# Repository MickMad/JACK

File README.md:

#JACK
##Just Another Cortex Kit

A Cortex-M0+ development kit with an Atmel SAM D21, a USB device port, a regulator, some passives, a programming header, and breakout headers.

Arduino Zero compatible.

Software is here:

https://github.com/MickMad/ArduinoCore-samd/

```
Copyright © Michele Perla 2015

This documentation describes Open Hardware and is licensed under the CERN OHL v. 1.2.
You may redistribute and modify this documentation under the terms of the CERN OHL v.1.2. 
(http://ohwr.org/cernohl). This documentation is distributed
WITHOUT ANY EXPRESS OR IMPLIED WARRANTY, INCLUDING OF
MERCHANTABILITY, SATISFACTORY QUALITY AND FITNESS FOR A
PARTICULAR PURPOSE. Please see the CERN OHL v.1.2 for applicable
conditions
```

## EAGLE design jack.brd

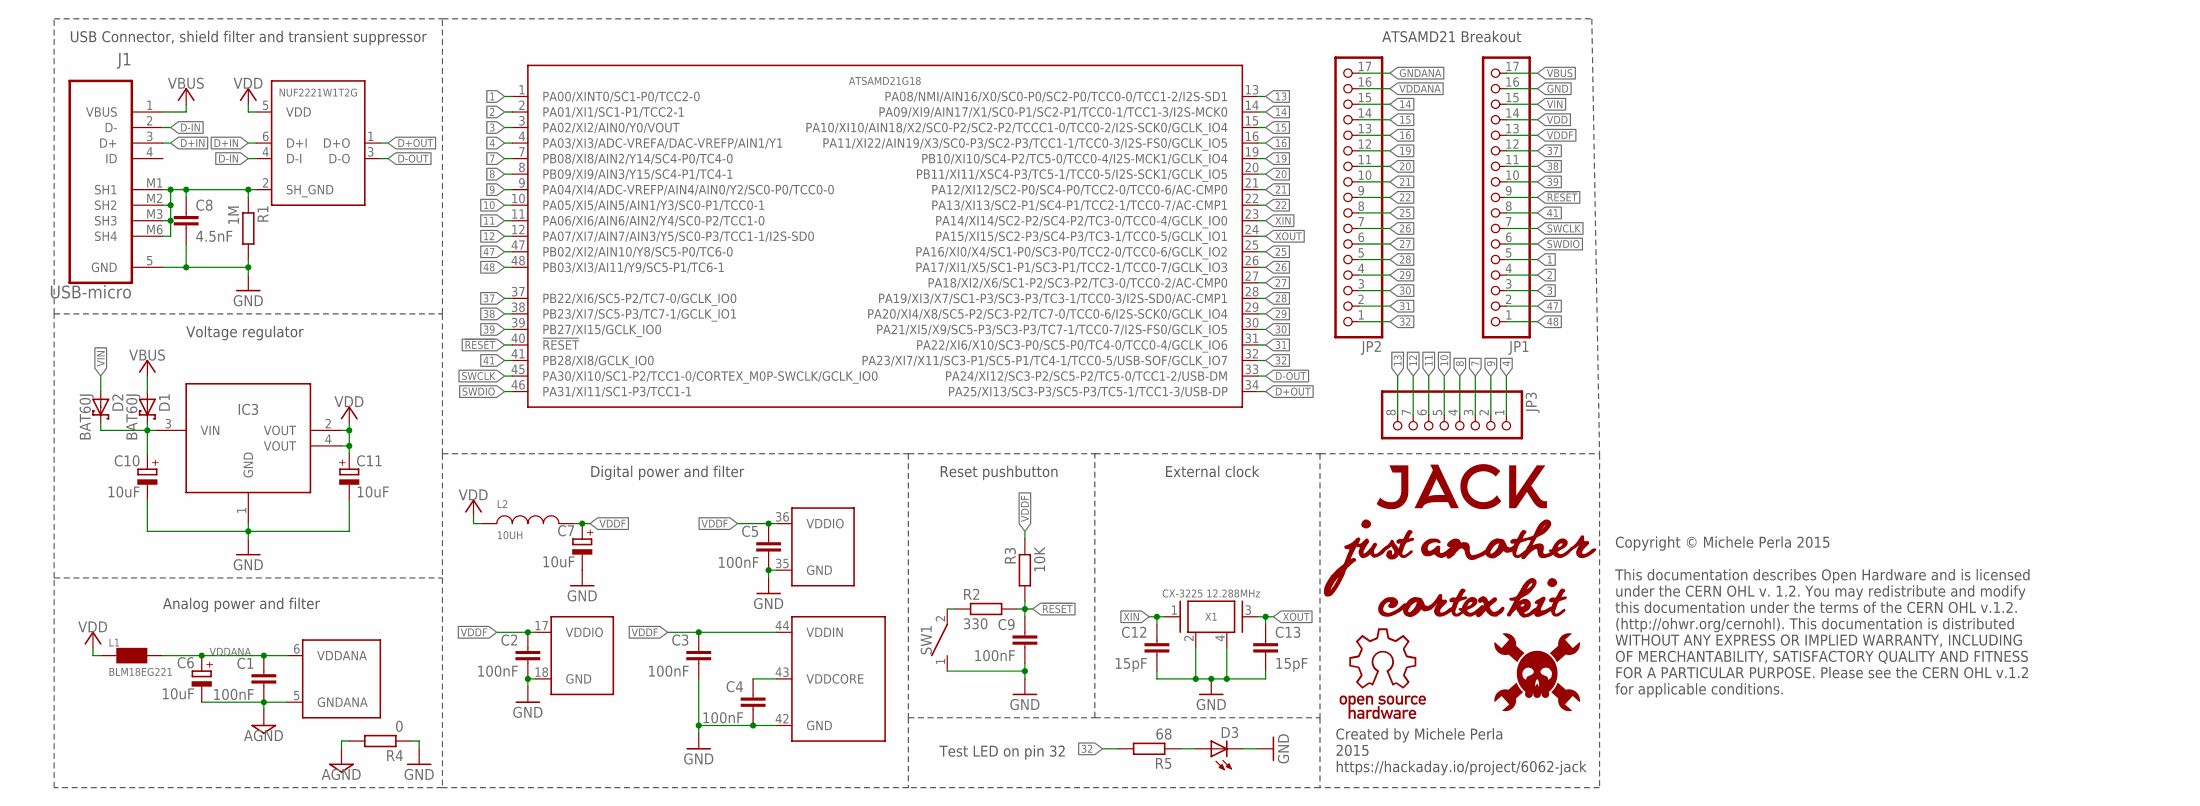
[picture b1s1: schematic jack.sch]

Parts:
C1, C2, C3, C4, C5, C9: 100nF; C0402
C6, C7, C10, C11: 10uF; CT3216
C8: 4.5nF; C0402
C12, C13: 15pF; C0402
D1, D2: BAT60J; SOD323_ST
D3: LED; LED-0603
IC1: NUF2221W1T2G; SOT-363
IC2: ATSAMD21G18; TQFP48
IC3: LDO; SOT-223-3
J1: USB-micro; MOLEX_47346-0001
JP1, JP2: PINHD-1X17; 1X17
JP3: PINHD-1X8; 1X08
L1: BLM18EG221; 0603
L2: 10UH; IND_ELLVXG
R1: 1M; R0603
R2: 330; R0603
R3: 10K; R0603
R4: 0; R0603
R5: 68; R0603
SW1: SPST3.5X6MM; SWITCH-SMD-3.5X6MM
U$3: JACK-LOGO
U$5: HAD-LOGO
U$6: OSHW-LOGO
X1: CX-3225 12.288MHz; CX-3225

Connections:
1: IC2.1 (PA00/XINT0/SC1-P0/TCC2-0), JP1.5
2: IC2.2 (PA01/XI1/SC1-P1/TCC2-1), JP1.4
3: IC2.3 (PA02/XI2/AIN0/Y0/VOUT), JP1.3
4: IC2.4 (PA03/XI3/ADC-VREFA/DAC-VREFP/AIN1/Y1), JP3.1
7: IC2.7 (PB08/XI8/AIN2/Y14/SC4-P0/TC4-0), JP3.3
8: IC2.8 (PB09/XI9/AIN3/Y15/SC4-P1/TC4-1), JP3.4
9: IC2.9 (PA04/XI4/ADC-VREFP/AIN4/AIN0/Y2/SC0-P0/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), JP3.2
10: IC2.10 (PA05/XI5/AIN5/AIN1/Y3/SC0-P1/TCC0-1), JP3.5
11: IC2.11 (PA06/XI6/AIN6/AIN2/Y4/SC0-P2/TCC1-0), JP3.6
12: IC2.12 (PA07/XI7/AIN7/AIN3/Y5/SC0-P3/TCC1-1/I2S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), JP3.7
13: IC2.13 (PA08/NMI/AIN16/X0/SC0-P0/SC2-P0/TCC0-0/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), JP3.8
14: IC2.14 (PA09/XI9/AIN17/X1/SC0-P1/SC2-P1/TCC0-1/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), JP2.15
15: IC2.15 (PA10/XI10/AIN18/X2/SC0-P2/SC2-P2/TCCC1-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), JP2.14
16: IC2.16 (PA11/XI22/AIN19/X3/SC0-P3/SC2-P3/TCC1-1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), JP2.13
19: IC2.19 (PB10/XI10/SC4-P2/TC5-0/TCC0-4/I2S-MCK1/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), JP2.12
20: IC2.20 (PB11/XI11/XSC4-P3/TC5-1/TCC0-5/I2S-SCK1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), JP2.11
21: IC2.21 (PA12/XI12/SC2-P0/SC4-P0/TCC2-0/TCC0-6/A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), JP2.10
22: IC2.22 (PA13/XI13/SC2-P1/SC4-P1/TCC2-1/TCC0-7/A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), JP2.9
25: IC2.25 (PA16/XI0/X4/SC1-P0/SC3-P0/TCC2-0/TCC0-6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), JP2.8
26: IC2.26 (PA17/XI1/X5/SC1-P1/SC3-P1/TCC2-1/TCC0-7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), JP2.7
27: IC2.27 (PA18/XI2/X6/SC1-P2/SC3-P2/TC3-0/TCC0-2/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), JP2.6
28: IC2.28 (PA19/XI3/X7/SC1-P3/SC3-P3/TC3-1/TCC0-3/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), JP2.5
29: IC2.29 (PA20/XI4/X8/SC5-P2/SC3-P2/TC7-0/TCC0-6/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), JP2.4
30: IC2.30 (PA21/XI5/X9/SC5-P3/SC3-P3/TC7-1/TCC0-7/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), JP2.3
31: IC2.31 (PA22/XI6/X10/SC3-P0/SC5-P0/TC4-0/TCC0-4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), JP2.2
32: IC2.32 (PA23/XI7/X11/SC3-P1/SC5-P1/TC4-1/TCC0-5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), JP2.1, R5.2
37: IC2.37 (PB22/XI6/SC5-P2/TC7-0/GCLK_IO0), JP1.12
38: IC2.38 (PB23/XI7/SC5-P3/TC7-1/GCLK_IO1), JP1.11
39: IC2.39 (PB27/XI15/GCLK_IO0), JP1.10
41: IC2.41 (PB28/XI8/GCLK_IO0), JP1.8
47: IC2.47 (PB02/XI2/AIN10/Y8/SC5-P0/TC6-0), JP1.2
48: IC2.48 (PB03/XI3/AI11/Y9/SC5-P1/TC6-1), JP1.1
!RESET: C9.1, IC2.40 (!RESET), JP1.9, R2.2, R3.2
D+IN: IC1.6 (D+I), J1.3 (D+)
D+OUT: IC1.1 (D+O), IC2.34 (PA25/XI13/SC3-P3/SC5-P3/TC5-1/TCC1-3/US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)
D-IN: IC1.4 (D-I), J1.2 (D-)
D-OUT: IC1.3 (D-O), IC2.33 (PA24/XI12/SC3-P2/SC5-P2/TC5-0/TCC1-2/US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)
GND: C2.2, C3.2, C4.2, C5.2, C7.-, C8.2, C9.2, C10.-, C11.-, C12.2, C13.2, D3.C, IC2.18 (GND), IC2.35 (GND), IC2.42 (GND), IC3.1 (GND), J1.5 (GND), JP1.16, R1.2, R4.1, SW1.1, X1.2 (GND), X1.4 (GND)
GNDANA: C1.2, C6.-, IC2.5 (GNDANA), JP2.17, R4.2
LDOIN: C10.+, D1.C, D2.C, IC3.3 (VIN)
unnamed: D3.A, R5.1
unnamed: R2.1, SW1.2
SH_GND: C8.1, IC1.2 (SH_GND), J1.M1 (SH1), J1.M2 (SH2), J1.M3 (SH3), J1.M6 (SH4), R1.1
SWCLK: IC2.45 (PA30/XI10/SC1-P2/TCC1-0/CORTEX_M0P-SWCL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), JP1.7
SWDIO: IC2.46 (PA31/XI11/SC1-P3/TCC1-1), JP1.6
VBUS: D1.A, J1.1 (VBUS), JP1.17
VDD: C11.+, IC1.5 (VDD), IC3.2 (VOUT), IC3.4 (VOUT), JP1.14, L1.1, L2.2
VDDANA: C1.1, C6.+, IC2.6 (VDDANA), JP2.16, L1.2
VDDCORE: C4.1, IC2.43 (VDDCORE)
VDDF: C2.1, C3.1, C5.1, C7.+, IC2.17 (VDDIO), IC2.36 (VDDIO), IC2.44 (VDDIN), JP1.13, L2.1, R3.1
VIN: D2.A, JP1.15
XIN: C12.1, IC2.23 (PA14/XI14/SC2-P2/SC4-P2/TC3-0/TCC0-4/GC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), X1.1
XOUT: C13.1, IC2.24 (PA15/XI15/SC2-P3/SC4-P3/TC3-1/TCC0-5/GC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), X1.3

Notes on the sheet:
USB Connector, shield filter and transient suppressor
Voltage regulator
Analog power and filter
Digital power and filter
Reset pushbutton
External clock
ATSAMD21 Breakout
Created by Michele Perla 2015 https://hackaday.io/project/6062-jack
Test LED on pin 32
Copyright © Michele Perla 2015 This documentation describes Open Hardware and is licensed under the CERN OHL v. 1.2. You may redistribute and modify this documentation under the terms of the CERN OHL v.1.2. (http://ohwr.org/cernohl). This documentation is distributed WITHOUT ANY EXPRESS OR IMPLIED 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

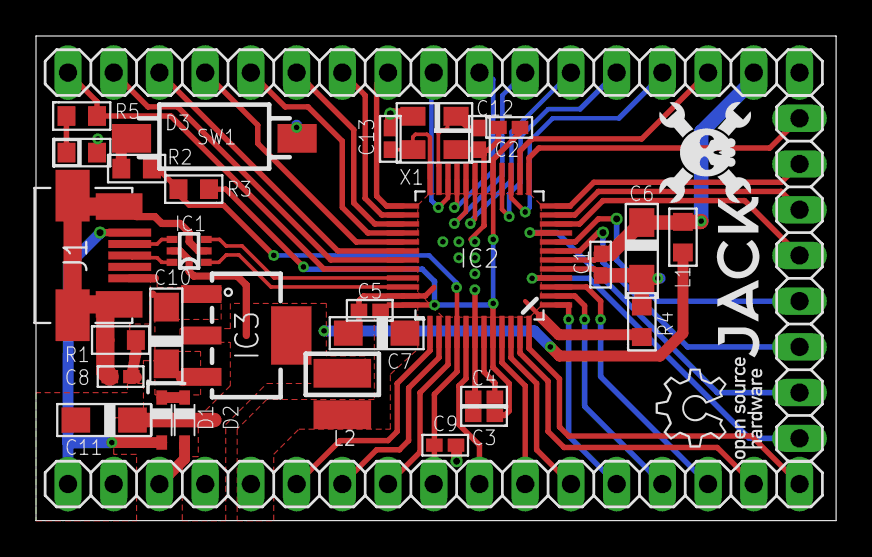
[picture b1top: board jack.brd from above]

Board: 2 copper layers, 44.5 x 26.9 mm, 35 parts (0 on the bottom side), 53 nets.

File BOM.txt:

Partlist exported from C:/Users/mperla.CORP/Documents/GitHub/JACK/jack.sch at 16/07/2015 16:05

Part Value             Device          Package            Description                                                            
C1   100nF             C-EU            C0402K                                                                                    
C2   100nF             C-EU            C0402K                                                                                    
C3   100nF             C-EU            C0402K                                                                                    
C4   100nF             C-EU            C0402K                                                                                    
C5   100nF             C-EU            C0402K                                                                                  
C9   100nF             C-EU            C0402K

C8   4.5nF             C-EU            C0402K  
                                                                                    
C6   10uF              CPOL-EU         SMC_P                                                                                     
C7   10uF              CPOL-EU         SMC_P                                                                                                                                                                        
C10  10uF              CPOL-EU         SMC_P                                                                                     
C11  10uF              CPOL-EU         SMC_P   
                                                                                  
C12  15pF              C-EU            C0402K                                                                                    
C13  15pF              C-EU            C0402K 
                                                                                   
D1   BAT60J            BAT60J          SOD323_ST          Schottky barrier diode                                                 
D2   BAT60J            BAT60J          SOD323_ST          Schottky barrier diode  
                                               
D3   LED               LED             LED-0603           Blue LED                                                               
IC1  NUF2221W1T2G      NUF2221W1T2G    SOT-363            ON SEMICONDUCTOR NUF2221W1T2G  IC, FILTER, USB, ESD PROTECTION, SOT363 
IC2  ATSAMD21G18       ATSAMD21G18     TQFP48                                                                                    
IC3  NCV1117ST33T3G    NCV1117ST33T3G  SOT-223-3          ON Semiconductor LDO 3.3V 1.0A Automotive                                                                       
J1   USB-micro         47346-0001      MOLEX_47346-0001   CONN RCPT 5POS MICRO USB R/A  SMD                                      

JP1                    PINHD-1X17      1X17               PIN HEADER                                                             
JP2                    PINHD-1X17      1X17               PIN HEADER                                                             
JP3                    PINHD-1X8       1X08               PIN HEADER  
                                                           
L1   BLM18EG221        L               0603               Ferrite bead                                                           
L2   10UH              ELLVFG100MC-VXG IND_ELLVXG         Choke Coils   
                                                         
R1   1M                R-EU            R0603                                                                                     
R2   330               R-EU            R0603                                                                                     
R3   10K               R-EU            R0603                                                                                     
R4   0                 R-EU            R0603                                                                                     
R5   68                R-EU            R0603     
                                                                                
SW1  SPST3.5X6MM       SPST3.5X6MM     SWITCH-SMD-3.5X6MM Tactile Switches 3.5X6 SMT TACT TACT SWITCH - Mouser part # 506-FSMSM                                                                                 
X1   CX-3225 12.288MHz XTALCX-3225     CX-3225

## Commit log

2015-06-01 :confetti_ball: Added .gitattributes & .gitignore files
2015-06-01 :boom: Added project, schematic, libraries and README files
2015-06-04 :grin: Added SPST symbol, modded SAMD21 pin names
    Added SPST symbol for the reset switch (still got to find a suitable
    tact switch), modified the SAMD21 pin names to show all their functions
2015-06-09 :+1: Added LDO and graphics
    Added 3.3 V LDO in library and schematic, added graphics for logo
    (temporary?)
2015-06-12 :goat: Added 24 MHZ crystal
    Added 24 MHZ crystal
2015-06-16 :memo: Added headers, protection diodes
    Added protection diodes (reverse voltage/current for external power
    input), dded pinout headers to schematic. Now I only got to decide how
    to arrange pins on the breakout :smile:
2015-06-17 :+1: Finished 1st schematic rev, created jack.brd
    Finished first schematic revision (pin layout), created jack.brd layout
    file, minor modifications to two downloaded component packages (text
    size and position)
2015-06-18 :octocat: Moved a few components on layout
    Started layout process.... I'm going really slow (work is a pain)
2015-06-25 :hatching_chick: Polished schematic, started layout
    I polished the schematic so to let people easily understand what does
    what, dividing it in sections with a description; I did a hi-res picture
    of it so to see it without having to open Eagle CAD; also, I started the
    layout process; you can already see on the PCB where stuff should go in
    the end
2015-06-25 :wavy_dash: Progressing with layout
    Still dealing with layout, in particular dealing with analog/digital
    power, decoupling caps and correct power grounding (one ground to rule
    them all, or local a/d planes near chip and then star ground near LDO?)
2015-06-26 Minor changes
2015-07-01 :satellite: Modified .gitignore, updated schematic, progressing layout
2015-07-01 :paperclip: Ultimating critical parts layout
    Finishing crystal, decoupling caps and USB signals an parts layout;
    trying to figure out where to move the rest...
2015-07-02 Started power signals layout
2015-07-02 :thumbsup: Updated mcu pins/breakout header map
    I'm mapping the pins of the ATSAM21D to the breakout header in a way
    that reduces airwires length on the PCB, thus easing the layout process
2015-07-06 PCB layout almost done, changed breakout configuration accordingly
2015-07-06 :feelsgood: Layout finished!
    Minor details gotta be worked now (polishing pours layout)
2015-07-07 :thumbsup: minor project update (polishing stuff)
    Added new screenshots, little tweaks to schematic and layout (ground
    fills, power signals fills). The design is still missing a logo though
2015-07-08 :feelsgood: Totally done now!
    Added LED on pin 23, added logos (hackaday, oshw, JACK)
2015-07-09 :octocat: Added stopmask on logos
    Now the logos will look all shiny and clear! woohoo
2015-07-09 :rage1: removed useless bmp import file produced by import-bmp.ulp
2015-07-10 :suspect: Revision 2! (pre-prototype fix)
    Changed 10uF to polarized tantalum caps, changed packages accordingly,
    had to move some stuff around, also had to add/resize some copper pours,
    finally added polarity marks and place marks on all parts to give a more
    detailed (readable) silk mask.
2015-07-15 :sleepy: Reduced board size!
    I managed to shrink the board in less than 3X5 cm^2. It now features an
    8 pin header on the left side so to let the board fit under 5 cm on both
    sides, to get cheapest PCB manufactury.
2015-07-16 Minor changes (added BOM)
2015-07-16 :grin: Added eagleUp folder, modded jack.lbr
    I'm testing 3D view of the PCB with components on it because it's cool
    and because it'll let me see if the components would overlap in real
    life. I'm also modding the jack.lbr file to show little squares around
    little parts on silkscreen, to triple-check packages sizes, and to match
    packages names with eagleUp model names. I'll eventually add the final
    SketchUp file of it.
2015-07-16 Updated .sch and .brd to match changes in library files
    Ops, I forgot to save and close the project before pushing the last
    commit :grin:
2015-07-23 :feelsgood: Added BOM, Gerbers, 3D model and render
2015-08-14 Updated BOM, JACK logo package, GERBERS, licence, readme
2015-08-14 Update of gerber files
2015-08-14 Added LICENCE_HOWTO.pdf
    Added usage guidelines of CERN OHL 1.2 licence as required by the
    licence
